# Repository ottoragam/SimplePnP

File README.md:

# SimplePnP
Your personal open-hardware PCB assembly machine

----------------------------------------------------------------------
SimplePnP (c) by Gino Magarotto

SimplePnP is licensed under a
Creative Commons Attribution-ShareAlike 3.0 Unported License.

You should have received a copy of the license along with this
work.  If not, see <http://creativecommons.org/licenses/by-sa/3.0/>.

----------------------------------------------------------------------

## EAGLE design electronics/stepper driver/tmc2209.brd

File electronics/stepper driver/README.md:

Carrier board for three TMC2209 stepper drivers. Standard and serial pins broken out. Fixed current limit.

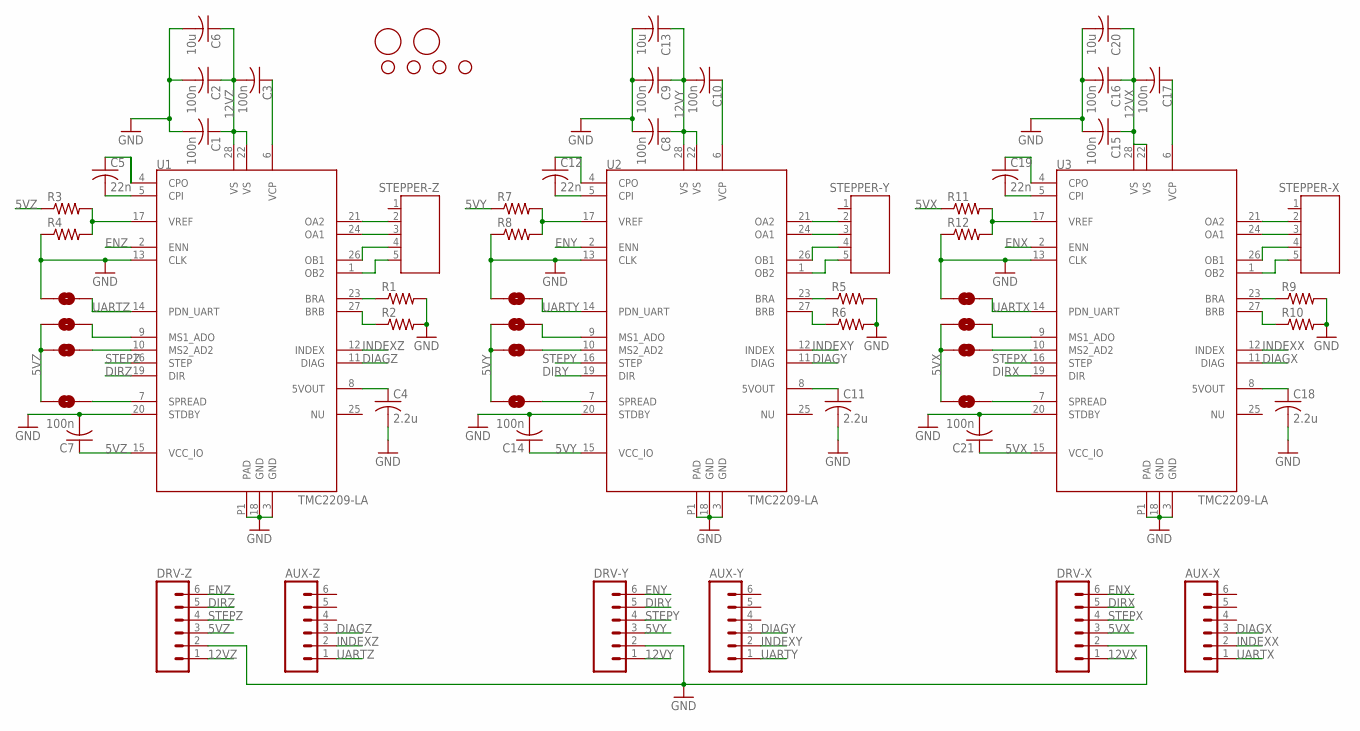
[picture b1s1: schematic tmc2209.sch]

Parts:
AUX-X: M06LOCK; 1X06_LOCK
AUX-Y: M06LOCK; 1X06_LOCK
AUX-Z: M06LOCK; 1X06_LOCK
C1, C2, C3, C7, C8, C9, C10, C14, C15, C16, C17, C21: 100n; C0603
C4, C11, C18: 2.2u; C1206
C5, C12, C19: 22n; C0603
C6, C13, C20: 10u; C1206
DRV-X: M06LOCK; 1X06_LOCK
DRV-Y: M06LOCK; 1X06_LOCK
DRV-Z: M06LOCK; 1X06_LOCK
PDX: SOLDERJUMPERNO; SJ_2S-NO
PDY: SOLDERJUMPERNO; SJ_2S-NO
PDZ: SOLDERJUMPERNO; SJ_2S-NO
R1, R2, R5, R6, R9, R10: R-US_R0805; R0805
R3, R4, R7, R8, R11, R12: R-US_R0603; R0603
SJ2, SJ3, SJ5, SJ6, SJ8, SJ9, SJ10, SJ11, SJ12: SOLDERJUMPERNO; SJ_2S-NO
STANDOFF1, STANDOFF2, STANDOFF3, STANDOFF4: STAND-OFFTIGHT; STAND-OFF-TIGHT
STEPPER-X: JST-PH5
STEPPER-Y: JST-PH5
STEPPER-Z: JST-PH5
U1, U2, U3: TMC2209-LA; QFN28-5X5-XLEP
U$1, U$2: FIDUCIAL; FIDUCIAL_1MM

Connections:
5VX: C21.1, DRV-X.3, R11.1, SJ8.1, SJ9.1, SJ12.1, U3.15 (VCC_IO)
5VY: C14.1, DRV-Y.3, R7.1, SJ5.1, SJ6.1, SJ11.1, U2.15 (VCC_IO)
5VZ: C7.1, DRV-Z.3, R3.1, SJ2.1, SJ3.1, SJ10.1, U1.15 (VCC_IO)
12VX: C15.1, C16.1, C17.2, C20.1, DRV-X.1, U3.22 (VS), U3.28 (VS)
12VY: C8.1, C9.1, C10.2, C13.1, DRV-Y.1, U2.22 (VS), U2.28 (VS)
12VZ: C1.1, C2.1, C3.2, C6.1, DRV-Z.1, U1.22 (VS), U1.28 (VS)
DIAGX: AUX-X.3, U3.11 (DIAG)
DIAGY: AUX-Y.3, U2.11 (DIAG)
DIAGZ: AUX-Z.3, U1.11 (DIAG)
DIRX: DRV-X.5, U3.19 (DIR)
DIRY: DRV-Y.5, U2.19 (DIR)
DIRZ: DRV-Z.5, U1.19 (DIR)
ENX: DRV-X.6, U3.2 (ENN)
ENY: DRV-Y.6, U2.2 (ENN)
ENZ: DRV-Z.6, U1.2 (ENN)
GND: C1.2, C2.2, C4.2, C6.2, C7.2, C8.2, C9.2, C11.2, C13.2, C14.2, C15.2, C16.2, C18.2, C20.2, C21.2, DRV-X.2, DRV-Y.2, DRV-Z.2, PDX.1, PDY.1, PDZ.1, R1.2, R2.2, R4.1, R5.2, R6.2, R8.1, R9.2, R10.2, R12.1, U1.3 (GND), U1.13 (CLK), U1.18 (GND), U1.20 (STDBY), U1.P1 (PAD), U2.3 (GND), U2.13 (CLK), U2.18 (GND), U2.20 (STDBY), U2.P1 (PAD), U3.3 (GND), U3.13 (CLK), U3.18 (GND), U3.20 (STDBY), U3.P1 (PAD)
INDEXX: AUX-X.2, U3.12 (INDEX)
INDEXY: AUX-Y.2, U2.12 (INDEX)
INDEXZ: AUX-Z.2, U1.12 (INDEX)
unnamed: STEPPER-Z.5, U1.1 (OB2)
unnamed: STEPPER-Z.4, U1.26 (OB1)
unnamed: STEPPER-Z.3, U1.24 (OA1)
unnamed: STEPPER-Z.2, U1.21 (OA2)
unnamed: STEPPER-Y.5, U2.1 (OB2)
unnamed: STEPPER-Y.4, U2.26 (OB1)
unnamed: STEPPER-Y.3, U2.24 (OA1)
unnamed: STEPPER-Y.2, U2.21 (OA2)
unnamed: STEPPER-X.2, U3.21 (OA2)
unnamed: STEPPER-X.3, U3.24 (OA1)
unnamed: STEPPER-X.4, U3.26 (OB1)
unnamed: STEPPER-X.5, U3.1 (OB2)
unnamed: R5.1, U2.23 (BRA)
unnamed: C11.1, U2.8 (5VOUT)
unnamed: SJ2.2, U1.9 (MS1_ADO)
unnamed: SJ3.2, U1.10 (MS2_AD2)
unnamed: SJ6.2, U2.10 (MS2_AD2)
unnamed: R6.1, U2.27 (BRB)
unnamed: C18.1, U3.8 (5VOUT)
unnamed: C17.1, U3.6 (VCP)
unnamed: C12.2, U2.5 (CPI)
unnamed: C12.1, U2.4 (CPO)
unnamed: C19.2, U3.5 (CPI)
unnamed: SJ5.2, U2.9 (MS1_ADO)
unnamed: C19.1, U3.4 (CPO)
unnamed: SJ12.2, U3.7 (SPREAD)
unnamed: SJ11.2, U2.7 (SPREAD)
unnamed: SJ9.2, U3.10 (MS2_AD2)
unnamed: SJ8.2, U3.9 (MS1_ADO)
unnamed: R11.2, R12.2, U3.17 (VREF)
unnamed: R7.2, R8.2, U2.17 (VREF)
unnamed: C10.1, U2.6 (VCP)
unnamed: SJ10.2, U1.7 (SPREAD)
unnamed: R9.1, U3.23 (BRA)
unnamed: R10.1, U3.27 (BRB)
unnamed: R1.1, U1.23 (BRA)
unnamed: R2.1, U1.27 (BRB)
unnamed: R3.2, R4.2, U1.17 (VREF)
unnamed: C4.1, U1.8 (5VOUT)
unnamed: C5.2, U1.5 (CPI)
unnamed: C5.1, U1.4 (CPO)
unnamed: C3.1, U1.6 (VCP)
STEPX: DRV-X.4, U3.16 (STEP)
STEPY: DRV-Y.4, U2.16 (STEP)
STEPZ: DRV-Z.4, U1.16 (STEP)
UARTX: AUX-X.1, PDX.2, U3.14 (PDN_UART)
UARTY: AUX-Y.1, PDY.2, U2.14 (PDN_UART)
UARTZ: AUX-Z.1, PDZ.2, U1.14 (PDN_UART)

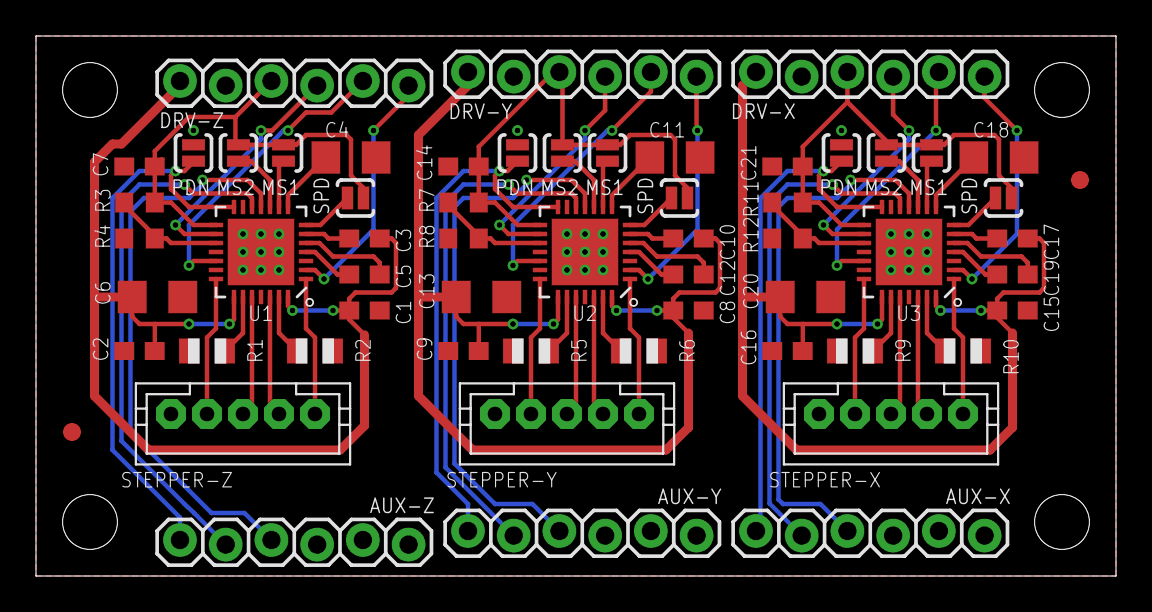
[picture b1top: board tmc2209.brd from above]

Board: 2 copper layers, 60.0 x 30.0 mm, 63 parts (0 on the bottom side), 67 nets.

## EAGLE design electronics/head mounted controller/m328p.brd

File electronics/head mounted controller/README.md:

Small form factor ATmega328p based GRBL booard. Connects to TMC2209 stepper driver board.

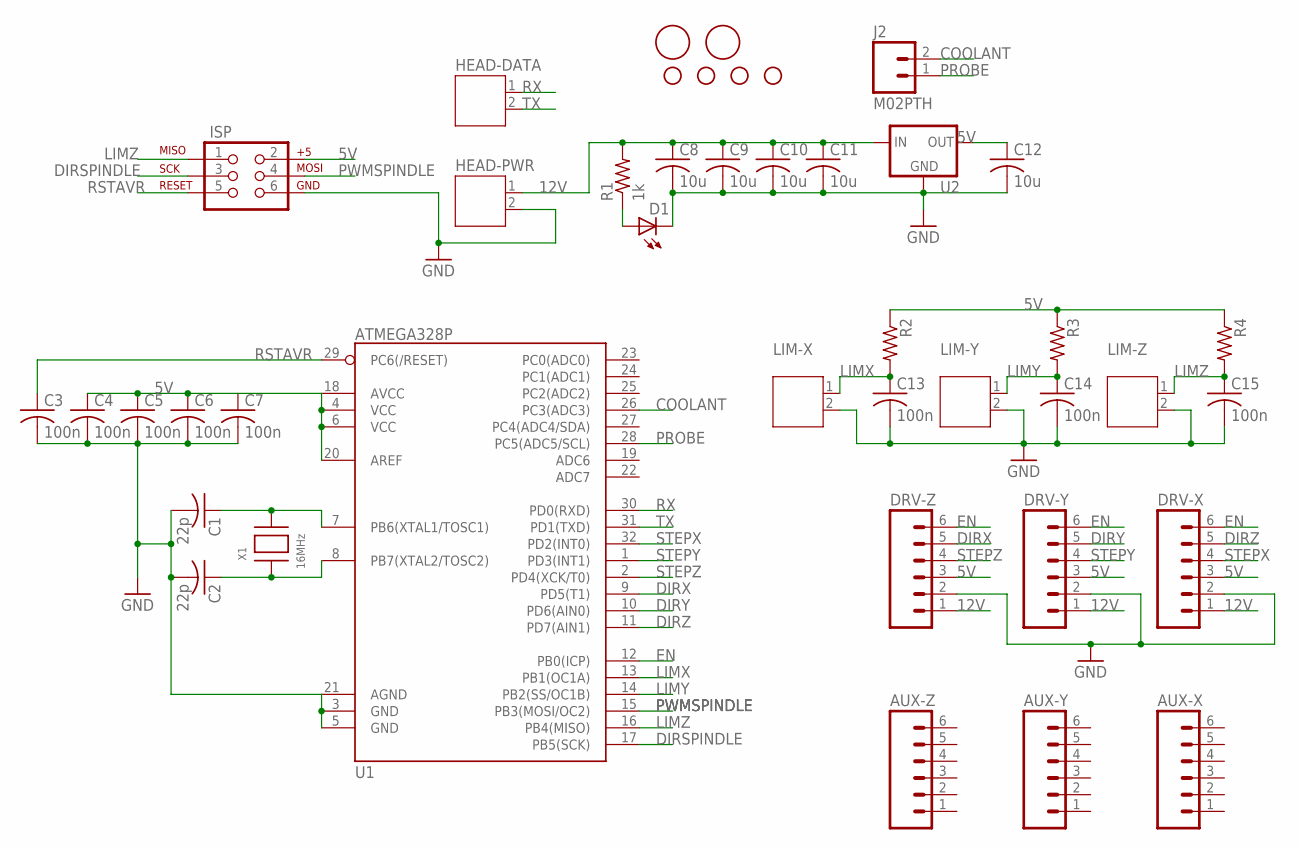
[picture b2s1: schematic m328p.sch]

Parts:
AUX-X: M06LOCK; 1X06_LOCK
AUX-Y: M06LOCK; 1X06_LOCK
AUX-Z: M06LOCK; 1X06_LOCK
C1, C2: 22p; C0603
C3, C4, C5, C6, C7, C13, C14, C15: 100n; C0603
C8, C9, C10, C11, C12: 10u; C1206
D1: LEDCHIPLED_1206; CHIPLED_1206
DRV-X: M06LOCK; 1X06_LOCK
DRV-Y: M06LOCK; 1X06_LOCK
DRV-Z: M06LOCK; 1X06_LOCK
HEAD-DATA: JST-PH2
HEAD-PWR: JST-PH2
ISP: AVR_SPI_PRG_6PTH; 2X3
J2: M02PTH; 1X02
LIM-X: JST-PH2
LIM-Y: JST-PH2
LIM-Z: JST-PH2
R1: 1k; R1206
R2, R3, R4: R-US_R0603; R0603
STANDOFF1, STANDOFF2, STANDOFF3, STANDOFF4: STAND-OFFTIGHT; STAND-OFF-TIGHT
U1: ATMEGA328P; TQFP32-08
U2: V_REG_MIC2920; SOT223
U$1, U$2: FIDUCIAL; FIDUCIAL_1MM
X1: 16MHz; XTAL3215

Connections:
5V: C4.1, C5.1, C6.1, C7.1, C12.1, DRV-X.3, DRV-Y.3, DRV-Z.3, ISP.2, R2.1, R3.1, R4.1, U1.4 (VCC), U1.6 (VCC), U1.18 (AVCC), U1.20 (AREF), U2.3 (OUT)
12V: C8.1, C9.1, C10.1, C11.1, DRV-X.1, DRV-Y.1, DRV-Z.1, HEAD-PWR.1, R1.2, U2.1 (IN)
COOLANT: J2.2, U1.26 (PC3(ADC3))
DIRSPINDLE: ISP.3, U1.17 (PB5(SCK))
DIRX: DRV-Z.5, U1.9 (PD5(T1))
DIRY: DRV-Y.5, U1.10 (PD6(AIN0))
DIRZ: DRV-X.5, U1.11 (PD7(AIN1))
EN: DRV-X.6, DRV-Y.6, DRV-Z.6, U1.12 (PB0(ICP))
GND: C1.2, C2.2, C3.2, C4.2, C5.2, C6.2, C7.2, C8.2, C9.2, C10.2, C11.2, C12.2, C13.2, C14.2, C15.2, D1.C, DRV-X.2, DRV-Y.2, DRV-Z.2, HEAD-PWR.2, ISP.6, LIM-X.2, LIM-Y.2, LIM-Z.2, U1.3 (GND), U1.5 (GND), U1.21 (AGND), U2.2 (GND), U2.4 (GND)
LIMX: C13.1, LIM-X.1, R2.2, U1.13 (PB1(OC1A))
LIMY: C14.1, LIM-Y.1, R3.2, U1.14 (PB2(SS/OC1B))
LIMZ: C15.1, ISP.1, LIM-Z.1, R4.2, U1.16 (PB4(MISO))
unnamed: C1.1, U1.7 (PB6(XTAL1/TOSC1)), X1.P$2
unnamed: C2.1, U1.8 (PB7(XTAL2/TOSC2)), X1.P$1
unnamed: D1.A, R1.1
PROBE: J2.1, U1.28 (PC5(ADC5/SCL))
PWMSPINDLE: ISP.4, U1.15 (PB3(MOSI/OC2))
RSTAVR: C3.1, ISP.5, U1.29 (PC6(/RESET))
RX: HEAD-DATA.1, U1.30 (PD0(RXD))
STEPX: DRV-X.4, U1.32 (PD2(INT0))
STEPY: DRV-Y.4, U1.1 (PD3(INT1))
STEPZ: DRV-Z.4, U1.2 (PD4(XCK/T0))
TX: HEAD-DATA.2, U1.31 (PD1(TXD))

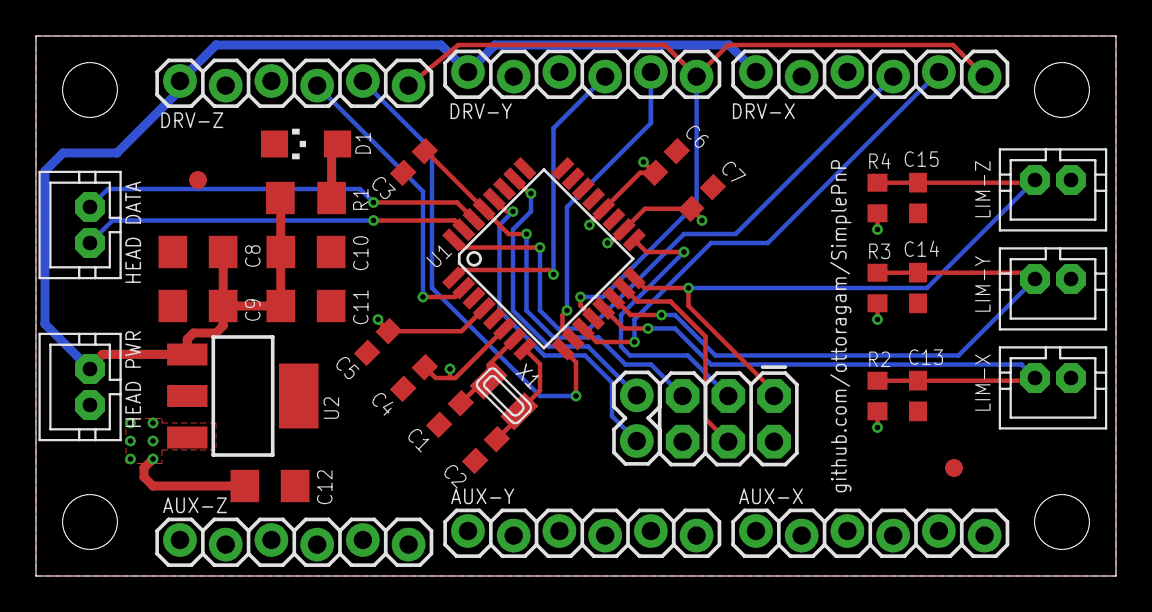
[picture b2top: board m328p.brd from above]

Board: 2 copper layers, 60.0 x 30.0 mm, 42 parts (0 on the bottom side), 23 nets.

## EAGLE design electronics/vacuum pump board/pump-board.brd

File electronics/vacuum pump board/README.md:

Mosfet switch board for 12VDC vacuum pump. Solder the motor terminals directly to the PCB.

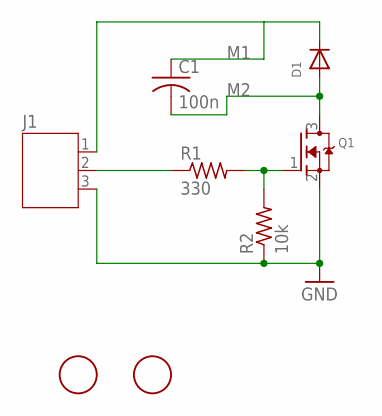
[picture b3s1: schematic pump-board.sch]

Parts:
C1: 100n; C1206
D1: DIODESOD-123; SOD-123
J1: JST-PH3
Q1: MOSFET-NREFLOW; SOT23
R1: 330; R1206
R2: 10k; R1206
U$1, U$2: FIDUCIAL; FIDUCIAL_1MM

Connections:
GATE: Q1.1 (G), R1.2, R2.2
GND: J1.3, Q1.2 (S), R2.1
M1: C1.1, D1.C, J1.1
M2: C1.2, D1.A, Q1.3 (D)
unnamed: J1.2, R1.1

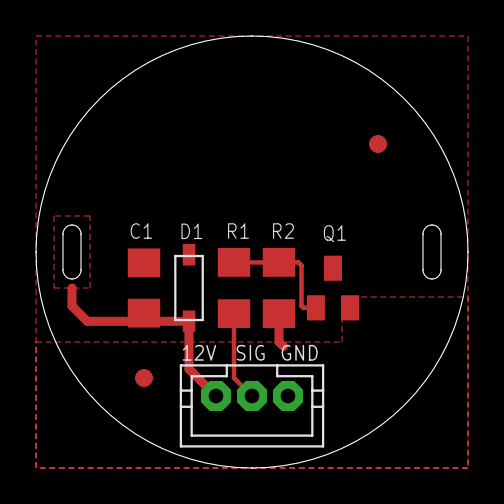
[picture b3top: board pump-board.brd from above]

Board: 2 copper layers, 24.0 x 24.0 mm, 8 parts (0 on the bottom side), 5 nets.

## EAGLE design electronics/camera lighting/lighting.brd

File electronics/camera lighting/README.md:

LED carrier board for pick and place camera illumination. 5V PWM input.

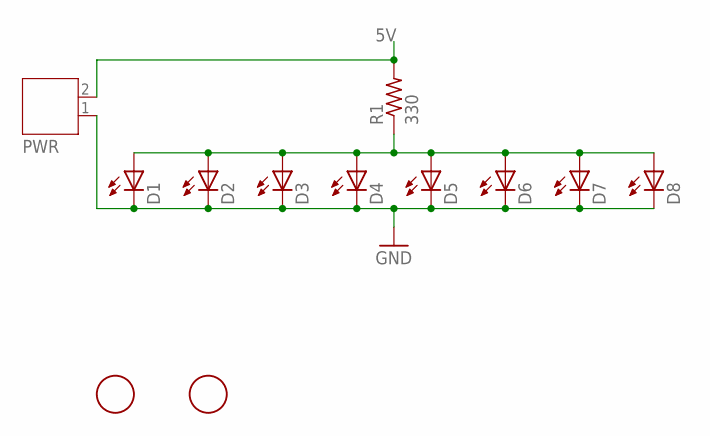
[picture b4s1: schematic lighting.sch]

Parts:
D1, D2, D3, D4, D5, D6, D7, D8: LEDCHIPLED_1206; CHIPLED_1206
PWR: JST-PH2
R1: 330; R1206
U$1, U$2: FIDUCIAL; FIDUCIAL_1MM

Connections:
5V: PWR.2, R1.2
COMMON: D1.A, D2.A, D3.A, D4.A, D5.A, D6.A, D7.A, D8.A, R1.1
GND: D1.C, D2.C, D3.C, D4.C, D5.C, D6.C, D7.C, D8.C, PWR.1

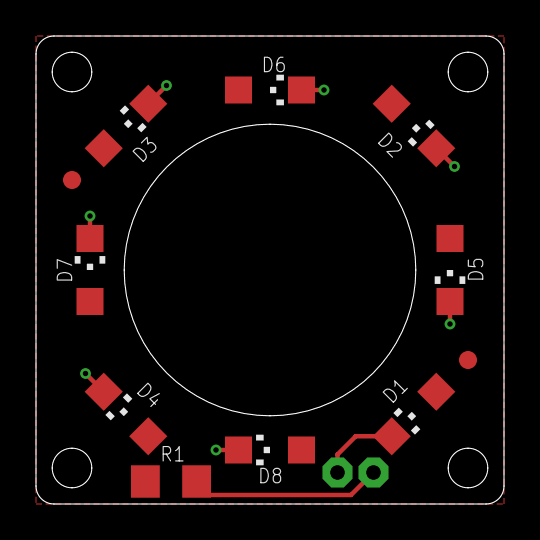
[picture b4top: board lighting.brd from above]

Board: 2 copper layers, 26.0 x 26.0 mm, 12 parts (1 on the bottom side), 3 nets.

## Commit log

2019-12-14 added prototype 2D drawings
2019-12-14 simplepnp-fullview
2019-12-14 various docs
2019-12-14 pnp manuals
2019-12-14 updated license
2019-12-14 render image
2019-12-15 xml configuration file for prototype machine
2019-12-17 partial BOM
2019-12-18 subject to change
2019-12-18 added missig item
2019-12-19 camera spacer
2019-12-19 more updates
2019-12-30 add M2 bolts
2019-12-30 added more stuff
2020-01-17 head mounted grbl
2020-01-26 prper directories and description
2020-01-28 camera lighting
2020-01-28 added description file
2020-01-28 back mounted pump PCB. Net tested for fit
2020-02-02 pre-production PCBs
2020-02-03 updated all PCBs and added PDF schematics
2020-03-04 Rename the electronic's *.md to README.md
2020-07-16 production design files
2020-07-16 added part

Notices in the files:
parts and their libraries:
SparkFun-Aesthetics: Licensing: Creative Commons ShareAlike 4.0 International - https://creativecommons.org/licenses/by-sa/4.0
